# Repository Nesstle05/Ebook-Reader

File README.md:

# Ebook-Reader

### Pasii de implementare
* Am creat schematicul 2D.
* Am creat PCB-ul, am intampinat niste erori:
    * **Via(hole) error** la componenta USB: am modificat footprint-ul componentei.
    * **Wire to wire error**: am rutat firele manual
* Am atribuit fiecarei componente din library cate un model 3D, si am creat placa 3d (*Push to 3D*)
* Am creat modelele pentru Display si Baterie dupa specificatiile din datasheeturi

## Diagrama bloc

## Utilizarea Pinilor ESP32-C6

Următorul tabel detaliază pinii GPIO specifici utilizați pe modulul ESP32-C6-WROOM-1 și funcțiile acestora în cadrul acestui proiect:

| Pin ESP32-C6 | Funcție                           | Component(e) Conectat(e)               | Interfață/Motiv                                              |
| :----------- | :-------------------------------- | :------------------------------------- | :----------------------------------------------------------- |
| GPIO0        | Selecție Boot / Intrare Buton     | SW_BOOT (Buton Boot), R_BOOT         | Pin standard pentru selecția modului boot; Intrare utilizator |
| GPIO1        | Ceas I2C                          | U4 (MAX17048), U3 (DS3231), SENSOR2 (BME688), J5 (Qwiic) | Magistrală I2C comună (SCL) pentru multipli senzori/CI        |
| GPIO2        | Date I2C                          | U4 (MAX17048), U3 (DS3231), SENSOR2 (BME688), J5 (Qwiic) | Magistrală I2C comună (SDA) pentru multipli senzori/CI        |
| GPIO3        | Selecție Cip E-Paper              | J1 (Header EPD)                        | Selecție Cip SPI (CS) pentru Afișajul E-Paper              |
| GPIO4        | Dată/Comandă E-Paper              | J1 (Header EPD)                        | Control Dată/Comandă (DC) pentru Afișajul E-Paper          |
| GPIO5        | Reset E-Paper                     | J1 (Header EPD)                        | Semnal Reset (RST) pentru Afișajul E-Paper               |
| GPIO6        | Stare Ocupat E-Paper              | J1 (Header EPD)                        | Semnal intrare Ocupat (Busy) de la Afișajul E-Paper          |
| GPIO7        | Hold Flash Extern                 | U1 (W25Q64JV), TP17                    | Semnal SPI Hold (/HOLD) pentru memoria flash externă         |
| GPIO8        | Dată 0 Card SD                    | J2 (Slot Card SD), TP6                 | Linie Date SDIO 0 / SPI MISO                               |
| GPIO9        | Dată 1 Card SD                    | J2 (Slot Card SD), TP7                 | Linie Date SDIO 1                                          |
| GPIO10       | Comandă Card SD                   | J2 (Slot Card SD), TP5                 | Linie Comandă SDIO / SPI MOSI                              |
| GPIO11       | Ceas Card SD                      | J2 (Slot Card SD), TP4                 | Linie Ceas SDIO / SPI SCK                                  |
| GPIO12       | Protecție Scriere Flash Extern    | U1 (W25Q64JV), TP16                    | Semnal SPI Protecție Scriere (/WP) pentru flash extern      |
| GPIO13       | MISO Flash Extern                 | U1 (W25Q64JV), TP15                    | SPI Master In Slave Out (MISO) pentru flash extern         |
| GPIO14       | MOSI Flash Extern                 | U1 (W25Q64JV), TP14                    | SPI Master Out Slave In (MOSI) pentru flash extern         |
| GPIO15       | Selecție Cip Flash Extern         | U1 (W25Q64JV), TP13                    | Selecție Cip SPI (/CS) pentru memoria flash externă        |
| GPIO16       | UART TXD                          | TP12                                   | Date Transmise UART pentru depanare/programare             |
| GPIO17       | UART RXD                          | TP11                                   | Date Recepționate UART pentru depanare/programare          |
| GPIO18       | Ceas Flash Extern                 | U1 (W25Q64JV), TP3                     | Ceas SPI (SCK) pentru memoria flash externă                |
| GPIO19       | Dată 2 Card SD                    | J2 (Slot Card SD), TP8                 | Linie Date SDIO 2                                          |
| GPIO20       | Dată 3 Card SD / Detectare Card   | J2 (Slot Card SD), TP9                 | Linie Date SDIO 3 / Intrare Detectare Card                 |
| GPIO21       | Intrare Buton Change              | SW_CHANGE (Buton Change)               | Intrare de Uz General pentru interacțiune utilizator         |
| USB_D-       | Date Negative USB                 | J4 (Conector USB-C)                    | Semnal Nativ USB D-                                        |
| USB_D+       | Date Pozitive USB                 | J4 (Conector USB-C)                    | Semnal Nativ USB D+                                        |
| EN           | Activare Sistem / Reset           | U5 (BD5229G), SW_RESET (Buton Reset)   | Activare Cip, controlat de supervizor tensiune/buton       |

## Energy management

| Component                   | Power Supply (V) | Estimated Current (mA) | Estimated Power (W) | Notes                                                                  |
|-----------------------------|-------------------|------------------------|----------------------|------------------------------------------------------------------------|
| ESP32-C6-WROOM-1-N8         | 3.3               | 150 (average)          | 0.5                  | Active mode; varies significantly based on usage.                       |
| SD Card Module              | 3.3               | 10 (average)           | 0.033                | Intermittent read/write operations.                                     |
| E-Paper Display             | 3.3               | 1(average)             | 0.0033               | Power used only during updates, very low average.                   |
| RTC Module - DS3231SN       | 3.3               | 1                      | 0.0033               |                                                                        |
| LiPo Fuel Gauger (MAX17048) | 3.3               | 0.05                   | 0.000165             | Very low power consumption.                                            |
| BME688 (Environmental Sensor) | 3.3               | 1 (average)            | 0.0033               | Intermittent readings.                                                  |
| NORFlash64MB (External Flash)| 3.3               | 2 (average)            | 0.0066               | Intermittent read/write operations.                                     |
| LDO Voltage Regulator       | 5 (input) / 3.3 (output) | Variable             | Variable               | Efficiency depends on load; quiescent current is very low.             |
| USB-C Connector + ESD       | 5 (input)         | Variable               | Variable               | Power depends on charging current; ESD protection negligible.          |
| Reset/Boot Buttons          | N/A               | Negligible             | Negligible           |                                                                        |
| **Total (Approximate)** |                   |          150-200              | **~0.55** | This is a rough estimate; actual power depends on duty cycles and usage. |

## Bill Of Materials (BOM)
| Componenta | Achizitie | Datasheet |
| ---------- | --------- | --------- |
| PFMF.050.1 | [Cumpara](https://ro.mouser.com/ProductDetail/Schurter/PFMF.050.2?qs=1auRipcfynCums5v1iucSA%3D%3D) |  [Datasheet](https://ro.mouser.com/datasheet/2/358/typ_PFMF-1275918.pdf) |
| USB4110-GF-A | [Cumpara](https://ro.mouser.com/ProductDetail/GCT/USB4110-GF-A?qs=KUoIvG%2F9IlYiZvIXQjyJeA%3D%3D) | [Datasheet](https://ro.mouser.com/datasheet/2/837/GCT_USB4110_Product_Drawing___20k_cycles-3455479.pdf) |
| USBLC6-2SC6Y | [Cumpara](https://ro.mouser.com/ProductDetail/STMicroelectronics/USBLC6-2SC6Y?qs=gNDSiZmRJS%2FOgDexvXkdow%3D%3D) | [Datasheet](https://ro.mouser.com/datasheet/2/389/usblc6_2sc6y-1852505.pdf) |
| SD0805S020S1R0 | [Cumpara](https://ro.mouser.com/ProductDetail/KYOCERA-AVX/SD0805S020S1R0?qs=jCA%252BPfw4LHbpkAoSnwrdjw%3D%3D) | [Datasheet](https://ro.mouser.com/datasheet/2/40/schottky-3165252.pdf) |
| DMG2305UX-7 | [Cumpara](https://ro.mouser.com/ProductDetail/Diodes-Incorporated/DMG2305UX-7?qs=L1DZKBg7t5F%2FNBHrjfxC%252Bg%3D%3D) | [Datasheet](https://www.diodes.com/assets/Datasheets/DMG2305UX.pdf) |
| XC6220A331MR-G | [Cumpara](https://ro.mouser.com/ProductDetail/Torex-Semiconductor/XC6220A331MR-G?qs=AsjdqWjXhJ8ZSWznL1J0gg%3D%3D) | [Datasheet](https://ro.mouser.com/datasheet/2/760/xc6220-3371556.pdf) |
| Condensator 100 uF TANT | [Cumpara](https://ro.mouser.com/ProductDetail/KYOCERA-AVX/TAJW107M010RNJ?qs=Wtp%252Bf%2FAeVqIH8v1VxV%252B1Rg%3D%3D) | [Datasheet](https://ro.mouser.com/datasheet/2/40/TAJ-3165264.pdf) |
| 112A-TAAR-R03_ATTEND | [Cumpara](https://www.digikey.ro/en/products/detail/attend-technology/112A-TAAR-R03/17633923) | [Datasheet](https://www.attend.com.tw/data/download/file/112A-TAAR-R03_Spec.pdf)
| ESP32-C6-WROOM-1-N8 | [Cumpara](https://ro.mouser.com/ProductDetail/Espressif-Systems/ESP32-C6-WROOM-1-N8?qs=8Wlm6%252BaMh8ST02Gmwp74cw%3D%3D) | [Datasheet](https://ro.mouser.com/datasheet/2/891/Espressif_ESP32_C6_WROOM_1__Datasheet_V0_1_PRELIMI-3239987.pdf) |
| MCP73831 | [Cumpara](https://ro.mouser.com/ProductDetail/Microchip-Technology/MCP73831T-2ACI-OT?qs=yUQqVecv4qvbBQBGbHx0Mw%3D%3D) | [Datasheet](https://ro.mouser.com/datasheet/2/268/MCP73831_Family_Data_Sheet_DS20001984H-3441711.pdf) |
| CHG_LED | [Cumpara](https://store.comet.srl.ro/Catalogue/Product/40478/) | [Datasheet](https://www.snapeda.com/parts/KP-1608SURCK/Kingbright/datasheet/) |
| SI1308EDL-T1-GE3 | [Cumpara](https://ro.mouser.com/ProductDetail/Vishay-Semiconductors/SI1308EDL-T1-GE3?qs=bX1%252BNvsK%2FBramh9tgpOaEw%3D%3D) | [Datasheet](https://www.vishay.com/doc?63399) |
| MBR0530 | [Cumpara](https://ro.mouser.com/ProductDetail/Micro-Commercial-Components-MCC/MBR0530-T?qs=9VyI4qLX4NTSXkb9ynzJnA%3D%3D) | [Datasheet](https://ro.mouser.com/datasheet/2/258/mcc_mbr0520~mbr0560sod123-1179695.pdf) |
| Bobina | [Cumpara](https://ro.mouser.com/ProductDetail/Wurth-Elektronik/744043680?qs=PGXP4M47uW6VkZq%252BkzjrHA%3D%3D) | [Datasheet](https://www.we-online.com/components/products/datasheet/744043680.pdf) |
| FH34SRJ-24S-0.5SH_99_ | [Cumpara](https://ro.mouser.com/ProductDetail/Hirose-Connector/FH34SRJ-24S-0.5SH99?qs=vcbW%252B4%252BSTIpKBl5ap9J8Fw%3D%3D) | [Datasheet](https://ro.mouser.com/datasheet/2/185/FH34SRJ_24S_0_5SH_99__CL0580_1255_6_99_2DDrawing_0-1615044.pdf) |
| BME688 | [Cumpara](https://ro.mouser.com/ProductDetail/Bosch-Sensortec/BME688?qs=IS%252B4QmGtzzqQoVDscqwx3A%3D%3D) | [Datasheet](https://ro.mouser.com/datasheet/2/783/bst_bme688_fl000-2307034.pdf) |
| BD5229G-TR | [Cumpara](https://ro.mouser.com/ProductDetail/ROHM-Semiconductor/BD5229G-TR?qs=4kLU8WoGk0vvnhrrYwdszw%3D%3D) | [Datasheet](https://fscdn.rohm.com/en/products/databook/datasheet/ic/power/voltage_detector/bd52xxg-e.pdf) |
| Buton adaptat | [Cumpara](https://ro.mouser.com/ProductDetail/CK/KMR221GULCLFS?qs=u2NJ%252B70r0goBXaNk7IrU0Q%3D%3D) | [Datasheet](https://www.ckswitches.com/media/1479/kmr2.pdf) |
| MAX17048G+T10 | [Cumpara](https://ro.mouser.com/ProductDetail/Analog-Devices-Maxim-Integrated/MAX17048G%2bT10?qs=D7PJwyCwLAoGnnn8jEPRBQ%3D%3D) | [Datasheet](https://ro.mouser.com/datasheet/2/609/MAX17048_MAX17049-3469099.pdf) |
| W25Q512JVEIQ | [Cumpara](https://ro.mouser.com/ProductDetail/Winbond/W25Q512JVEIQ?qs=l7cgNqFNU1jw6svr3at6tA%3D%3D) | [Datasheet](https://ro.mouser.com/datasheet/2/949/Winbond_W25Q512JV_Datasheet-3240039.pdf) |
| PGB1010603MR | [Cumpara](https://ro.mouser.com/ProductDetail/Littelfuse/PGB1010603MRHF?qs=KvZd0dN2Zg%2FuIq6icj%252BGKA%3D%3D) | [Datasheet](https://www.littelfuse.com/media?resourcetype=datasheets&itemid=8a337998-d54d-466b-be4e-dc5bcd1f9321&filename=littelfuse_pulseguard_pgb1_datasheet.pdf) |
| QWIIC_RIGHT_ANGLE | [Cumpara](https://ro.mouser.com/ProductDetail/GCT/USB4110-GF-A?qs=KUoIvG%2F9IlYiZvIXQjyJeA%3D%3D) | [Datasheet](https://ro.mouser.com/datasheet/2/837/GCT_USB4110_Product_Drawing___20k_cycles-3455479.pdf) |
| DS3231SN# | [Cumpara](https://ro.mouser.com/ProductDetail/Analog-Devices-Maxim-Integrated/DS3231SN?qs=ffX8NcjNb2RmKAb9wAk9Ug%3D%3D) | [Datasheet](https://ro.mouser.com/datasheet/2/609/DS3231-3421123.pdf) |
| CPH3225A C10_SUPERCAP | [Cumpara](https://ro.mouser.com/ProductDetail/Seiko-Semiconductors/CPH3225A?qs=3etwrb1wR%252BhUOph6lAO7eg%3D%3D) | [Datasheet](https://ro.mouser.com/datasheet/2/360/Seiko_Instruments_MicroBattery_E_20230330_2024Jan_-3561061.pdf) |
| Condensator 100nF | [Cumpara](https://ro.mouser.com/ProductDetail/KYOCERA-AVX/06033G104ZAT2A?qs=NXubJDmysXJMPmHfVo6Z%252BA%3D%3D) | [Datasheet](https://ro.mouser.com/datasheet/2/40/KGM_Y5V-3223189.pdf) |
| Condensator 4.7uF | [Cumpara](https://ro.mouser.com/ProductDetail/KYOCERA-AVX/0402ZD475MAT2A?qs=NBFAU1oqP4W4U2PCPHI0sg%3D%3D) | [Datasheet](https://ro.mouser.com/datasheet/2/40/cx5r_KGM-3223198.pdf) |
| Condensator 10uF | [Cumpara](https://ro.mouser.com/ProductDetail/Samsung-Electro-Mechanics/CL10A106KQ8NNNL?qs=xZ%2FP%252Ba9zWqaes9JKSsob2Q%3D%3D) | [Datasheet](https://ro.mouser.com/datasheet/2/585/MLCC-1837944.pdf) |
| Condensator 1uF/50V | [Cumpara](https://ro.mouser.com/ProductDetail/KYOCERA-AVX/06035D105MAT2A?qs=k4kUdCzLgS5%252BURKe1SOIeQ%3D%3D) | [Datasheet](https://ro.mouser.com/datasheet/2/40/cx5r_KGM-3223198.pdf) |
| Rezistenta 10K | [Cumpara](https://ro.mouser.com/ProductDetail/Vishay-Beyschlag/MCS0402MD1002BE000?qs=17u8i%2FzlE8%2F9BrAaXkMk1w%3D%3D) | [Datasheet](https://www.vishay.com/doc?28952) |
| Rezistenta 200 | [Cumpara](https://ro.mouser.com/ProductDetail/Vishay-Beyschlag/MCS0402MD2000BE100?qs=3SvaY9RawMJNVte4F12%252BZQ%3D%3D) | [Datasheet](https://www.vishay.com/doc?28952) |
| Rezistenta 100K | [Cumpara](https://ro.mouser.com/ProductDetail/Vishay-Beyschlag/MCT0603PD1003DP500?qs=5aG0NVq1C4wWAn8Ei3OpZA%3D%3D) | [Datasheet](https://www.vishay.com/doc?28916) |
| Rezistenta 2.2 | [Cumpara](https://ro.mouser.com/ProductDetail/SEI-Stackpole/RMCF0402FT2R20?qs=IPgv5n7u5QbBgyl0jwhwsA%3D%3D) | [Datasheet](https://ro.mouser.com/datasheet/2/385/SEI_RMCF_RMCP-3077565.pdf) |
| Rezistenta 5K1| [Cumpara](https://www.venkel.com/part/TFCR0603-16W-K-5690FT) | [Datasheet](https://data.venkel.com/documents/tfcr-series?_gl=1*tdo8m*_ga*NTA1MTc5MTcyLjE3NDM4OTMzNjc.*_ga_JRKGBZNVM8*MTc0Mzg5MzM2Ni4xLjAuMTc0Mzg5MzM2OC41OC4wLjA.) |
| Rezistenta 2K | [Cumpara](https://ro.mouser.com/ProductDetail/Vishay-Beyschlag/MCS04020C2001FE000?qs=wTZ%2FFzl837YG0wIkZJJOwQ%3D%3D) | [Datasheet](https://www.vishay.com/doc?28705) |
| Rezistenta 0.47 | [Cumpara](https://ro.mouser.com/ProductDetail/SEI-Stackpole/CSR0402JKR470?qs=IPgv5n7u5QawIB6nBEt8wA%3D%3D) | [Datasheet](https://ro.mouser.com/datasheet/2/385/SEI_CSR_CSRN-3077593.pdf) |
| Rezistenta 15 | [Cumpara](https://ro.mouser.com/ProductDetail/YAGEO/RT0402FRE0715RL?qs=BXCcY9r%252B08DFFpLSkPOIqQ%3D%3D) | [Datasheet](https://ro.mouser.com/datasheet/2/447/PYu_RT_1_to_0_01_RoHS_L_15-3461507.pdf) |

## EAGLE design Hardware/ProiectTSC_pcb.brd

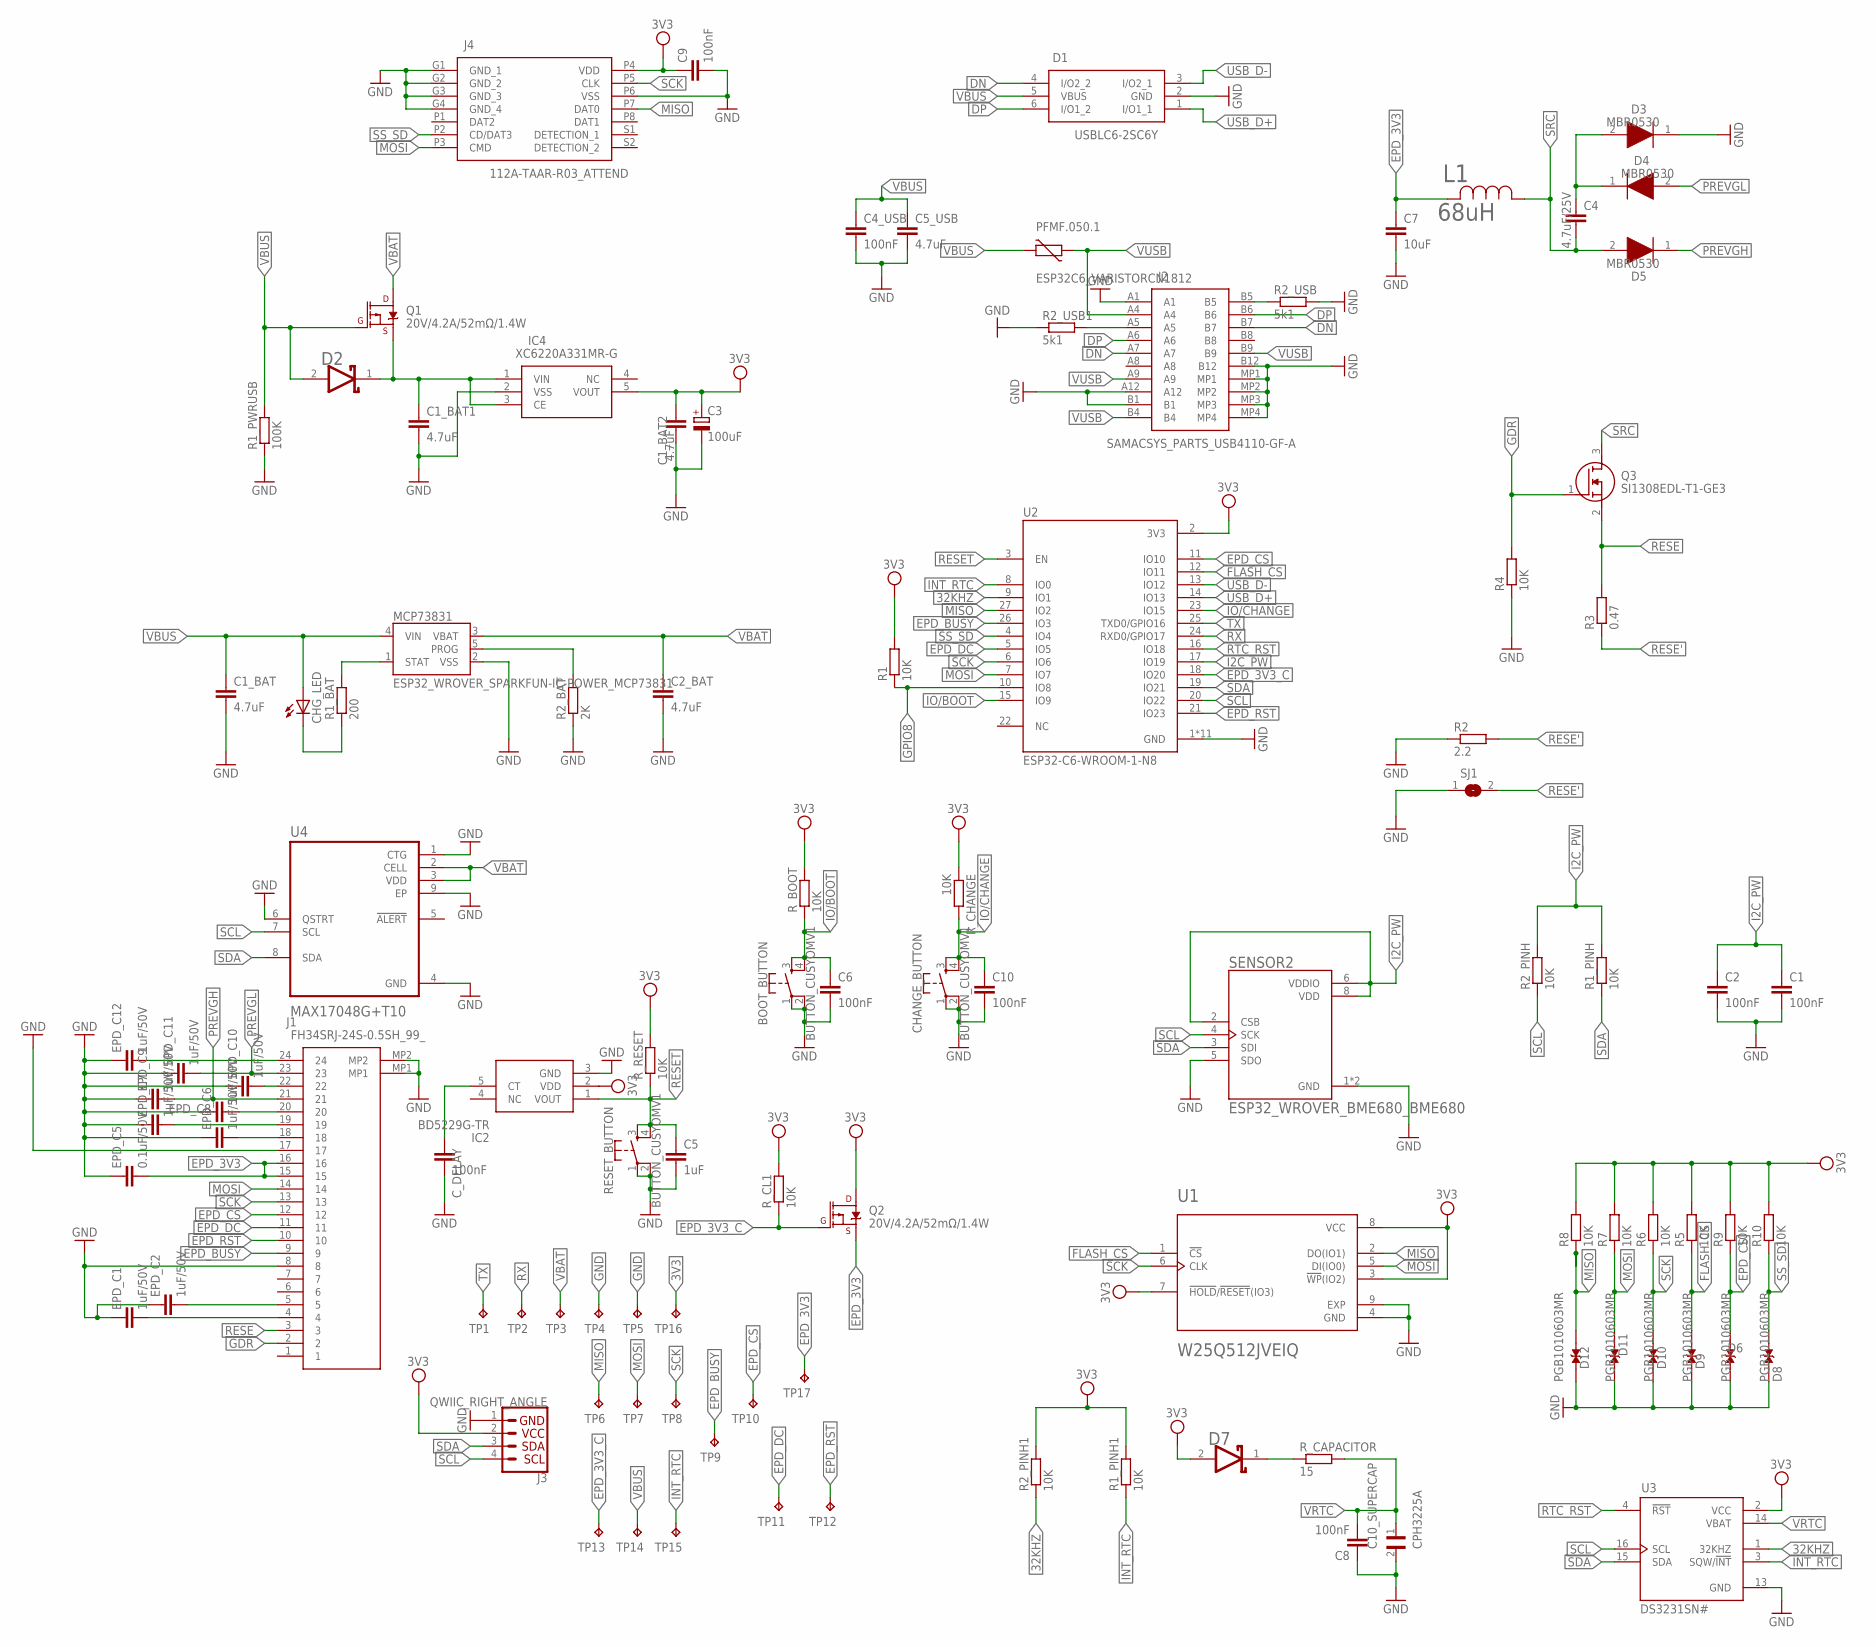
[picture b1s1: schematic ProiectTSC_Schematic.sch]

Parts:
BOOT_BUTTON: BUTTON_CUSYOMV1; MYBUTTON
C1, C2, C4_USB, C6, C8, C9, C10: 100nF; EAGLE-LTSPICE_C0402
C1_BAT, C1_BAT1, C1_BAT2, C2_BAT, C5_USB: 4.7uF; EAGLE-LTSPICE_C0402
C3: 100uF; RCL_CT3528
C4: 4.7uF/25V; EAGLE-LTSPICE_C0402
C5: 1uF; EAGLE-LTSPICE_C0402
C7: 10uF; EAGLE-LTSPICE_C0402
C10_SUPERCAP: CPH3225A; CAPCP3225X100N
CHANGE_BUTTON: BUTTON_CUSYOMV1; MYBUTTON
CHG_LED: ADAFRUIT_LEDCHIP-LED0603; ADAFRUIT_CHIP-LED0603
C_DELAY: 100nF; EAGLE-LTSPICE_C0402
D1: USBLC6-2SC6Y; SOT95P280X145-6N
D2, D7: ESP32_WROVER_AVX---SD0805S020S1R0_AVX_SD0805S020S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; ESP32_WROVER_AVX---SD0805S020S1R0_AVX_SD0805S020S1R0_0
D3, D4, D5: MBR0530; SOD3716X135N
D6, D8, D9, D10, D11, D12: PGB1010603MR; DIOC1608X36N
EPD_C1, EPD_C2, EPD_C6, EPD_C7, EPD_C8, EPD_C9, EPD_C10, EPD_C11, EPD_C12: 1uF/50V; EAGLE-LTSPICE_C0402
EPD_C5: 0.1uF/50V; EAGLE-LTSPICE_C0402
IC2: BD5229G-TR; SOT95P280X125-5N
IC4: XC6220A331MR-G; SOT95P280X120-5N
J1: FH34SRJ-24S-0.5SH_99_; FH34SRJ24S05SH99
J2: SAMACSYS_PARTS_USB4110-GF-A; SAMACSYS_PARTS_USB4110GFA
J3: QWIIC_RIGHT_ANGLE; JST04_1MM_RA
J4: 112A-TAAR-R03_ATTEND; 112ATAARR03ATTEND
L1: 68uH; IND_4828-WE-TPC_WRE
MCP73831: ESP32_WROVER_SPARKFUN-IC-POWER_MCP73831; ESP32_WROVER_SPARKFUN-IC-POWER_SOT23-5
PFMF.050.1: ESP32C6_VARISTORCN1812; ESP32C6_VARISTOR_CT/CN1812
Q1, Q2: 20V/4.2A/52mΩ/1.4W; ESP32_WROVER_SPARKFUN-DISCRETESEMI_SOT23-3
Q3: SI1308EDL-T1-GE3; SOT65P210X110-3N
R1, R1_PINH, R1_PINH1, R2_PINH, R2_PINH1, R4, R5, R6, R7, R8, R9, R10: 10K; ESP32_WROVER_EAGLE-LTSPICE_R0402
R1_BAT: 200; ESP32_WROVER_EAGLE-LTSPICE_R0402
R1_PWRUSB: 100K; ESP32_WROVER_EAGLE-LTSPICE_R0402
R2: 2.2; ESP32_WROVER_EAGLE-LTSPICE_R0402
R2_BAT: 2K; ESP32_WROVER_EAGLE-LTSPICE_R0402
R2_USB, R2_USB1: 5k1; ESP32_WROVER_EAGLE-LTSPICE_R0402
R3: 0.47; ESP32_WROVER_EAGLE-LTSPICE_R0402
RESET_BUTTON: BUTTON_CUSYOMV1; MYBUTTON
R_BOOT: 10K; ESP32_WROVER_EAGLE-LTSPICE_R0402
R_CAPACITOR: 15; ESP32_WROVER_EAGLE-LTSPICE_R0402
R_CHANGE: 10K; ESP32_WROVER_EAGLE-LTSPICE_R0402
R_CL1: 10K; ESP32_WROVER_EAGLE-LTSPICE_R0402
R_RESET: 10K; ESP32_WROVER_EAGLE-LTSPICE_R0402
SENSOR2: ESP32_WROVER_BME680_BME680; ESP32_WROVER_BME680_PSON80P300X300X100-8N
SJ1: SJ
TP1, TP2, TP3, TP4, TP5, TP6, TP7, TP8, TP9, TP10, TP11, TP12, TP13, TP14, TP15, TP16, TP17: TPTP20R; TP20R
U1: W25Q512JVEIQ; SON127P600X800X80-9N
U2: ESP32-C6-WROOM-1-N8; XCVR_ESP32-C6-WROOM-1-N8
U3: DS3231SN#; SOIC127P1032X265-16N
U4: MAX17048G+T10; SON50P200X200X80-9N

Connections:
3V3: C1_BAT2.1, C3.+, C9.1, D7.2 (ANODE), IC2.2 (VDD), IC4.5 (VOUT), J3.2, J4.P4 (VDD), Q2.3 (D), R1.2, R1_PINH1.2, R2_PINH1.2, R5.2, R6.2, R7.2, R8.2, R9.2, R10.2, R_BOOT.2, R_CHANGE.1, R_CL1.2, R_RESET.2, TP16.TP, U1.3 (!WP!(IO2)), U1.7 (!HOLD!/!RESET!(IO3)), U1.8 (VCC), U2.2 (3V3), U3.2 (VCC)
32KHZ: R2_PINH1.1, U2.9 (IO1), U3.1 (32KHZ)
DN: D1.4 (I/O2_2), J2.A7, J2.B7
DP: D1.6 (I/O1_2), J2.A6, J2.B6
EPD_3V3: C7.1, EPD_C5.2, J1.15, J1.16, L1.2, Q2.2 (S), TP17.TP
EPD_3V3_C: Q2.1 (G), R_CL1.1, TP13.TP, U2.18 (IO20)
EPD_BUSY: J1.9, TP9.TP, U2.26 (IO3)
EPD_CS: D6.2, J1.12, R9.1, TP10.TP, U2.11 (IO10)
EPD_DC: J1.11, TP11.TP, U2.5 (IO5)
EPD_RST: J1.10, TP12.TP, U2.21 (IO23)
FLASH_CS: D9.2, R5.1, U1.1 (!CS), U2.12 (IO11)
GDR: J1.2, Q3.1 (G), R4.2
GND: BOOT_BUTTON.1, BOOT_BUTTON.2, C1.2, C1_BAT.2, C1_BAT1.2, C1_BAT2.2, C2.2, C2_BAT.2, C3.-, C4_USB.2, C5.2, C5_USB.2, C6.2, C7.2, C8.1, C9.2, C10.2, C10_SUPERCAP.2, CHANGE_BUTTON.1, CHANGE_BUTTON.2, C_DELAY.2, D1.2 (GND), D3.1 (K), D6.1, D8.1, D9.1, D10.1, D11.1, D12.1, EPD_C1.1, EPD_C2.1, EPD_C5.1, EPD_C6.1, EPD_C7.1, EPD_C8.1, EPD_C9.1, EPD_C10.1, EPD_C11.1, EPD_C12.1, IC2.3 (GND), IC4.2 (VSS), J1.8, J1.17, J1.MP1, J1.MP2, J2.A1, J2.A12, J2.B1, J2.B12, J2.MP1, J2.MP2, J2.MP3, J2.MP4, J3.1, J4.G1 (GND_1), J4.G2 (GND_2), J4.G3 (GND_3), J4.G4 (GND_4), J4.P6 (VSS), MCP73831.2 (VSS), R1_PWRUSB.1, R2.1, R2_BAT.1, R2_USB.2, R2_USB1.1, R4.1, RESET_BUTTON.1, RESET_BUTTON.2, SENSOR2.1 (GND), SENSOR2.5 (SDO), SENSOR2.7 (GND), SJ1.1, TP4.TP, TP5.TP, U1.4 (GND), U1.9 (EXP), U2.1 (GND), U2.28 (GND), U2.29_1 (GND), U2.29_2 (GND), U2.29_3 (GND), U2.29_4 (GND), U2.29_5 (GND), U2.29_6 (GND), U2.29_7 (GND), U2.29_8 (GND), U2.29_9 (GND), U3.13 (GND), U4.1 (CTG), U4.4 (GND), U4.6 (QSTRT), U4.9 (EP)
GPIO8: R1.1, U2.10 (IO8)
I2C_PW: C1.1, C2.1, R1_PINH.2, R2_PINH.2, SENSOR2.2 (CSB), SENSOR2.6 (VDDIO), SENSOR2.8 (VDD), U2.17 (IO19)
INT_RTC: R1_PINH1.1, TP15.TP, U2.8 (IO0), U3.3 (SQW/!INT)
IO/BOOT: BOOT_BUTTON.3, BOOT_BUTTON.4, C6.1, R_BOOT.1, U2.15 (IO9)
IO/CHANGE: C10.1, CHANGE_BUTTON.3, CHANGE_BUTTON.4, R_CHANGE.2, U2.23 (IO15)
MISO: D12.2, J4.P7 (DAT0), R8.1, TP6.TP, U1.2 (DO(IO1)), U2.27 (IO2)
MOSI: D11.2, J1.14, J4.P3 (CMD), R7.1, TP7.TP, U1.5 (DI(IO0)), U2.7 (IO7)
unnamed: C1_BAT1.1, D2.1 (CATHODE), IC4.1 (VIN), IC4.3 (CE), Q1.2 (S)
unnamed: MCP73831.1 (STAT), R1_BAT.2
unnamed: CHG_LED.C, R1_BAT.1
unnamed: MCP73831.5 (PROG), R2_BAT.2
unnamed: J2.B5, R2_USB.1
unnamed: J2.A5, R2_USB1.2
unnamed: C4.1, D3.2 (A), D4.1 (K)
unnamed: D7.1 (CATHODE), R_CAPACITOR.1
unnamed: C_DELAY.1, IC2.5 (CT)
unnamed: EPD_C12.2, J1.24
unnamed: EPD_C10.2, J1.22
unnamed: EPD_C8.2, J1.20
unnamed: EPD_C7.2, J1.19
unnamed: EPD_C6.2, J1.18
unnamed: EPD_C2.2, J1.5
unnamed: EPD_C1.2, J1.4
PREVGH: D5.1 (K), EPD_C9.2, J1.21
PREVGL: D4.2 (A), EPD_C11.2, J1.23
RESE: J1.3, Q3.2 (S), R3.2
RESE': R2.2, R3.1, SJ1.2
RESET: C5.1, IC2.1 (VOUT), RESET_BUTTON.3, RESET_BUTTON.4, R_RESET.1, U2.3 (EN)
RTC_RST: U2.16 (IO18), U3.4 (!RST)
RX: TP2.TP, U2.24 (RXD0/GPIO17)
SCK: D10.2, J1.13, J4.P5 (CLK), R6.1, TP8.TP, U1.6 (CLK), U2.6 (IO6)
SCL: J3.4, R2_PINH.1, SENSOR2.4 (SCK), U2.20 (IO22), U3.16 (SCL), U4.7 (SCL)
SDA: J3.3, R1_PINH.1, SENSOR2.3 (SDI), U2.19 (IO21), U3.15 (SDA), U4.8 (SDA)
SRC: C4.2, D5.2 (A), L1.1, Q3.3 (D)
SS_SD: D8.2, J4.P2 (CD/DAT3), R10.1, U2.4 (IO4)
TX: TP1.TP, U2.25 (TXD0/GPIO16)
USB_D+: D1.1 (I/O1_1), U2.14 (IO13)
USB_D-: D1.3 (I/O2_1), U2.13 (IO12)
VBAT: C2_BAT.1, MCP73831.3 (VBAT), Q1.3 (D), TP3.TP, U4.2 (CELL), U4.3 (VDD)
VBUS: C1_BAT.1, C4_USB.1, C5_USB.1, CHG_LED.A, D1.5 (VBUS), D2.2 (ANODE), MCP73831.4 (VIN), PFMF.050.1.2, Q1.1 (G), R1_PWRUSB.2, TP14.TP
VRTC: C8.2, C10_SUPERCAP.1, R_CAPACITOR.2, U3.14 (VBAT)
VUSB: J2.A4, J2.A9, J2.B4, J2.B9, PFMF.050.1.1

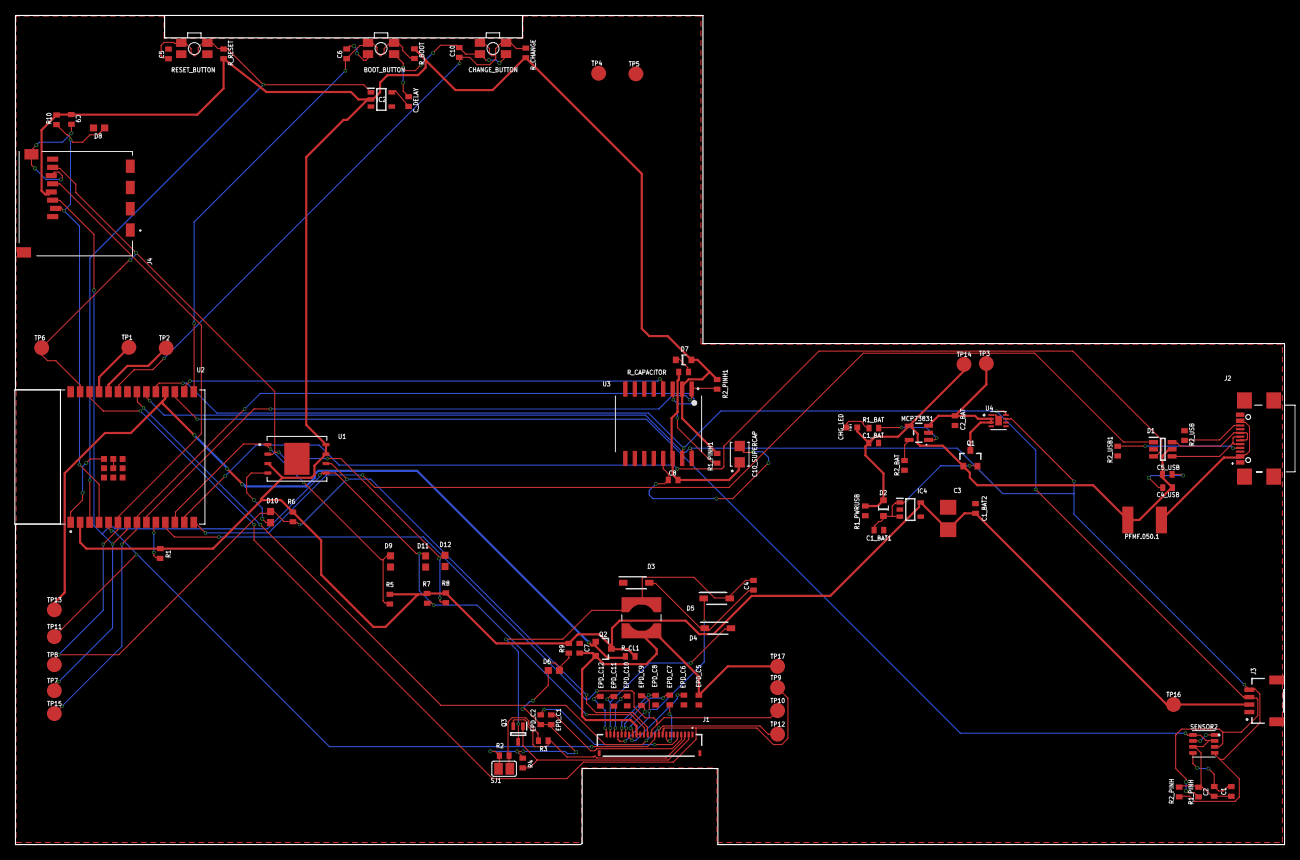
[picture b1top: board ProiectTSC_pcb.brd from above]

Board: 2 copper layers, 170.2 x 111.2 mm, 103 parts (0 on the bottom side), 55 nets.

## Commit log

2025-04-06 Create LICENSE

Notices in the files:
parts and their libraries:
DeskAssistant v19 v1: COPYRIGHT: Copyright (C) 2024 Ultra Librarian. All rights reserved.
